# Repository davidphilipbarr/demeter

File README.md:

# Demeter

Another 34 Key Keyboard with no diodes. 

Sadly this one does not use the cradio firmware, as it used a jumpered footprint for the controller.

There is a wired version for promicro type controllers and a bluetooth-first version for nice!nano type controllers. 

### Changes from the prototype:

* Pointless breakout pins removed.
* Silks removed/hidden.
* Slight edgecut adjustment.
* Wired version added as seperate board.

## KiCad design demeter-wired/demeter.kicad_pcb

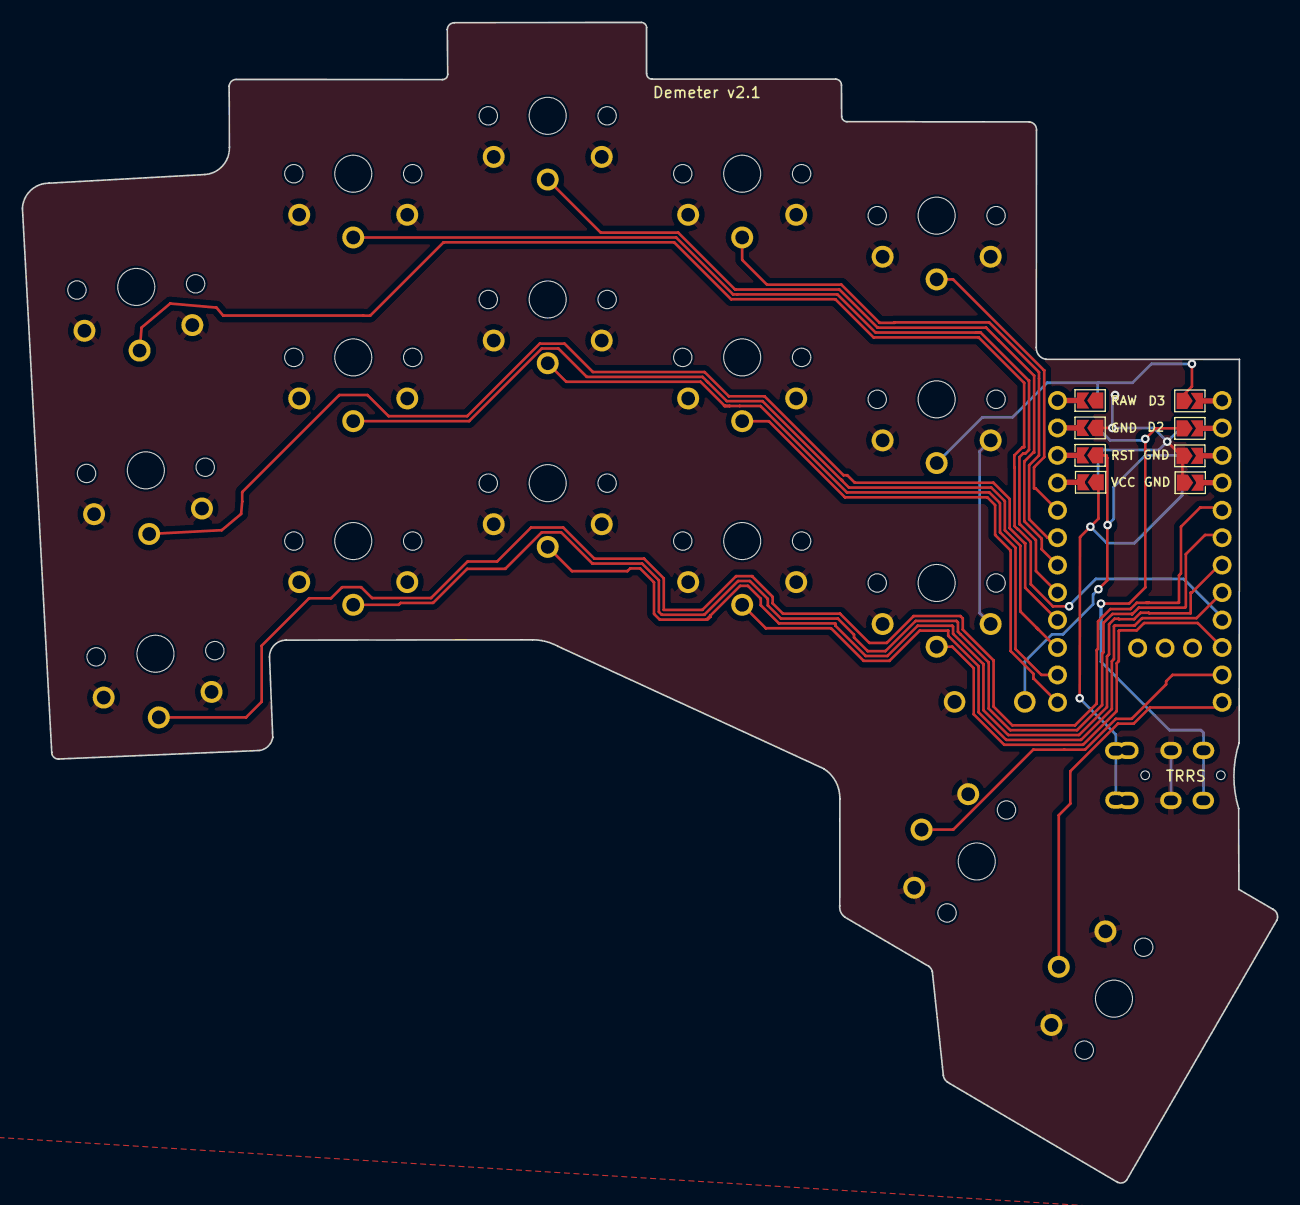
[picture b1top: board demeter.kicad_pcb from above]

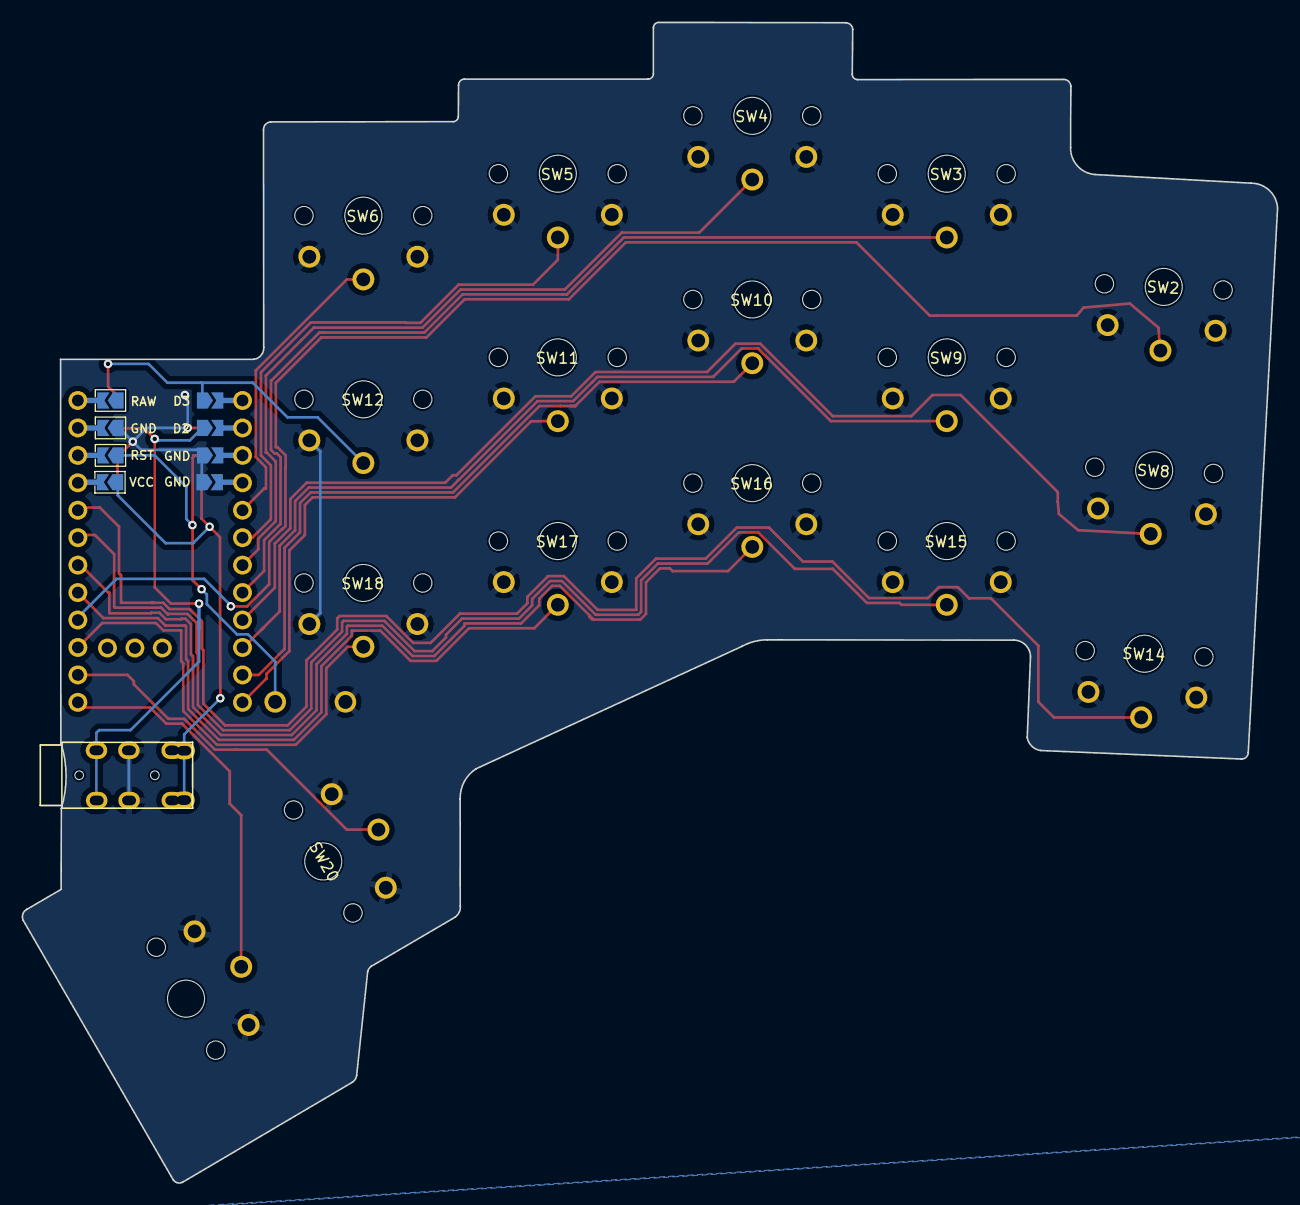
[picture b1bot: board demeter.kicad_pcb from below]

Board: 2 copper layers, 116.2 x 107.4 mm, 20 parts (2 on the bottom side), 21 nets.

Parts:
J2: AudioJack4dpb; TRRS-PJ-DPB2
RSW1: SW_Push; ResetSW
SW2, SW3, SW4, SW5, SW6, SW8, SW9, SW10, SW11, SW12, SW14, SW15, SW16, SW17, SW18, SW20: SW_Push; SW_PG1350_rev_DPB2.2
SW21: SW_Push; SW_PG1350_15_reversible_b2V2
U1: ProMicro-kbd; ProMicroSimpleJumperDPBnn2

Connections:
Switch1: SW2.1, U1.9 (D7)
Switch2: SW3.1, U1.17 (F7)
Switch3: SW4.1, U1.18 (F6)
Switch4: SW5.1, U1.19 (F5)
Switch5: SW6.1, U1.20 (F4)
Switch6: SW8.1, U1.16 (B1)
Switch7: SW9.1, U1.15 (B3)
Switch8: SW10.1, U1.14 (B2)
Switch9: SW11.1, U1.13 (B6)
Switch10: SW12.1, U1.1 (TX)
Switch11: SW14.1, U1.5 (SDA)
Switch12: SW15.1, U1.6 (SCL)
Switch13: SW16.1, U1.7 (D4)
Switch14: SW17.1, U1.8 (C6)
Switch15: SW18.1, U1.10 (E6)
Switch16: SW20.1, U1.11 (B4)
Switch17: SW21.1, U1.12 (B5)
Switch18: J2.R2, U1.2 (RX)
gnd: J2.R1, RSW1.1, SW2.2, SW3.2, SW4.2, SW5.2, SW6.2, SW8.2, SW9.2, SW10.2, SW11.2, SW12.2, SW14.2, SW15.2, SW16.2, SW17.2, SW18.2, SW20.2, SW21.2, U1.3 (GND), U1.4 (GND), U1.23 (GND)
reset: RSW1.2, U1.22 (RST)
vcc: J2.S, J2.T, U1.21 (VCC)

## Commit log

2024-01-31 initial upload
2024-01-31 add image of prototype
2024-01-31 Create README.md
    add rubbish readme
2024-02-01 spolling
